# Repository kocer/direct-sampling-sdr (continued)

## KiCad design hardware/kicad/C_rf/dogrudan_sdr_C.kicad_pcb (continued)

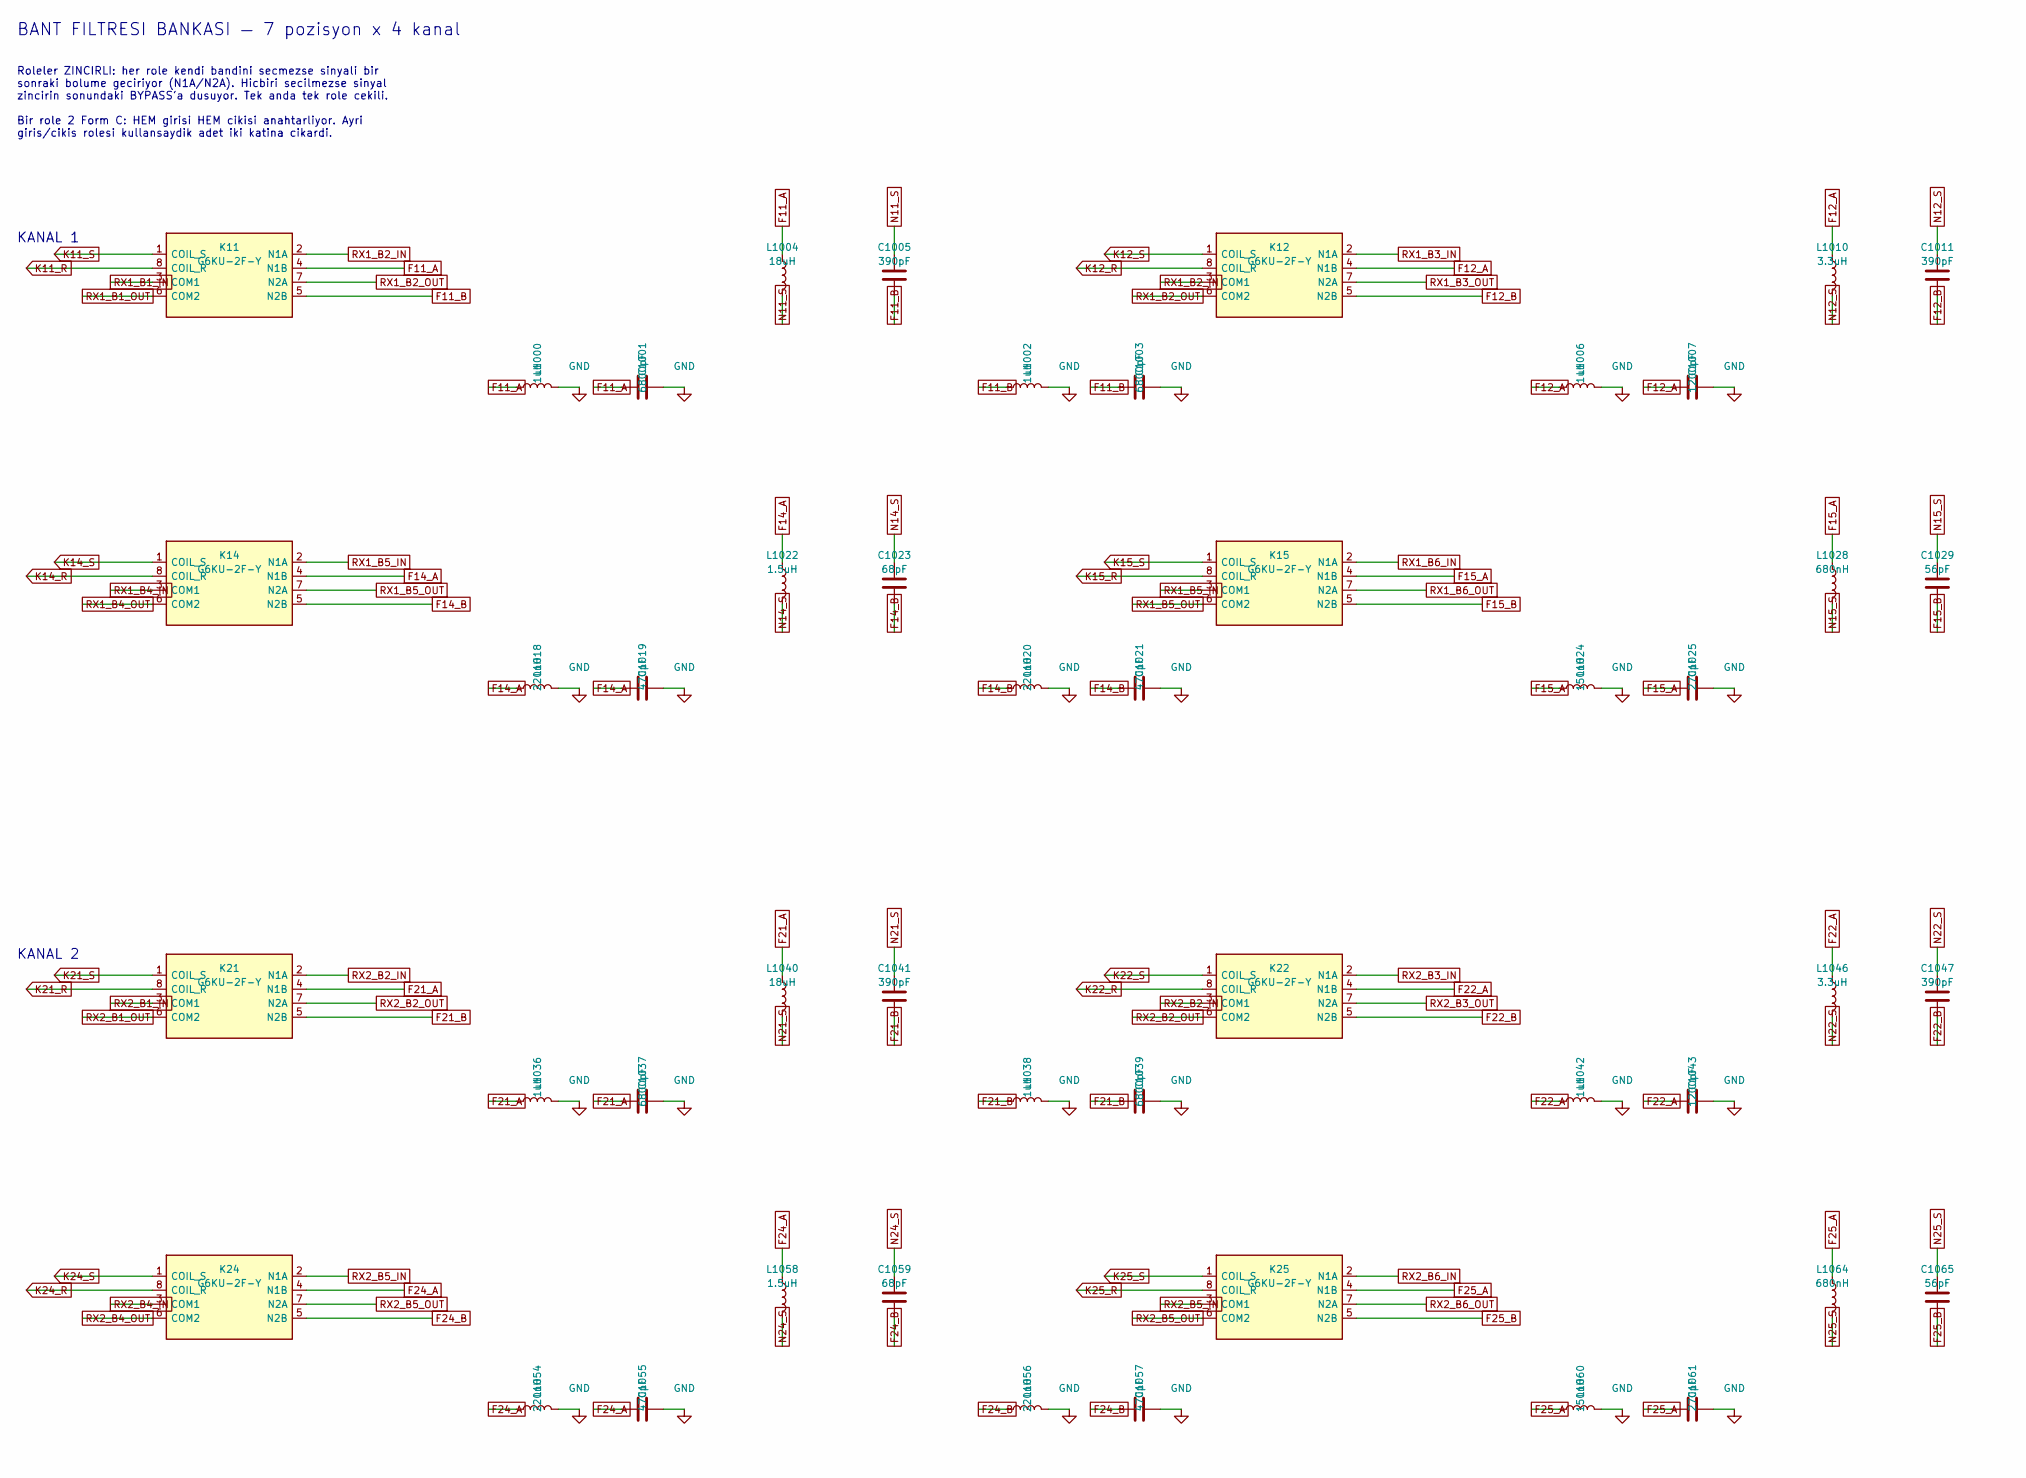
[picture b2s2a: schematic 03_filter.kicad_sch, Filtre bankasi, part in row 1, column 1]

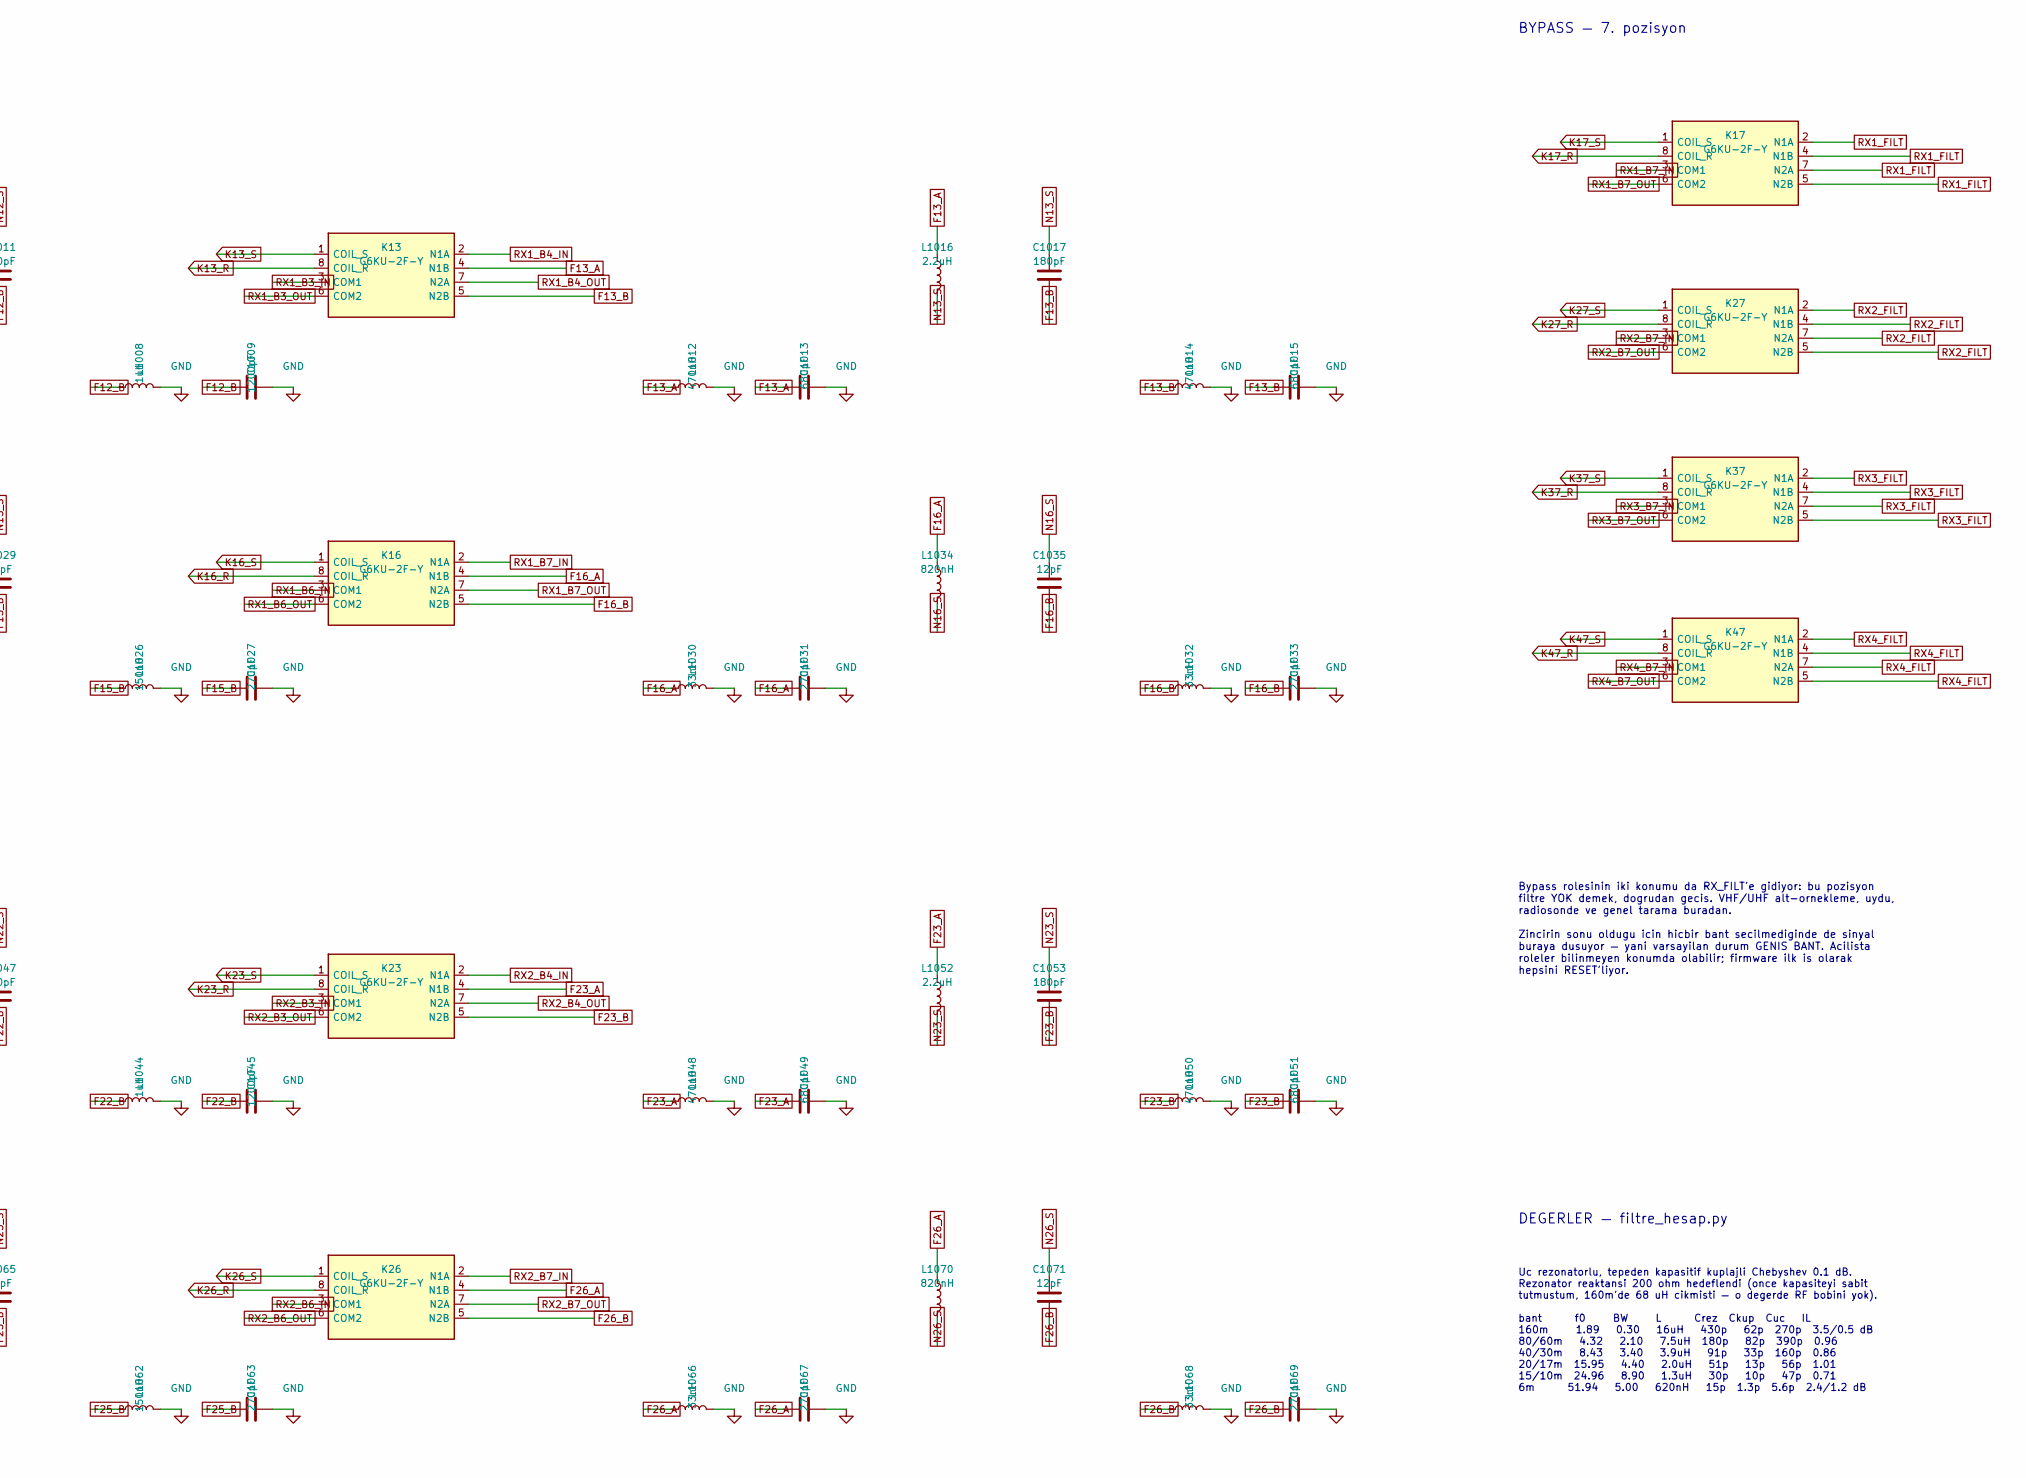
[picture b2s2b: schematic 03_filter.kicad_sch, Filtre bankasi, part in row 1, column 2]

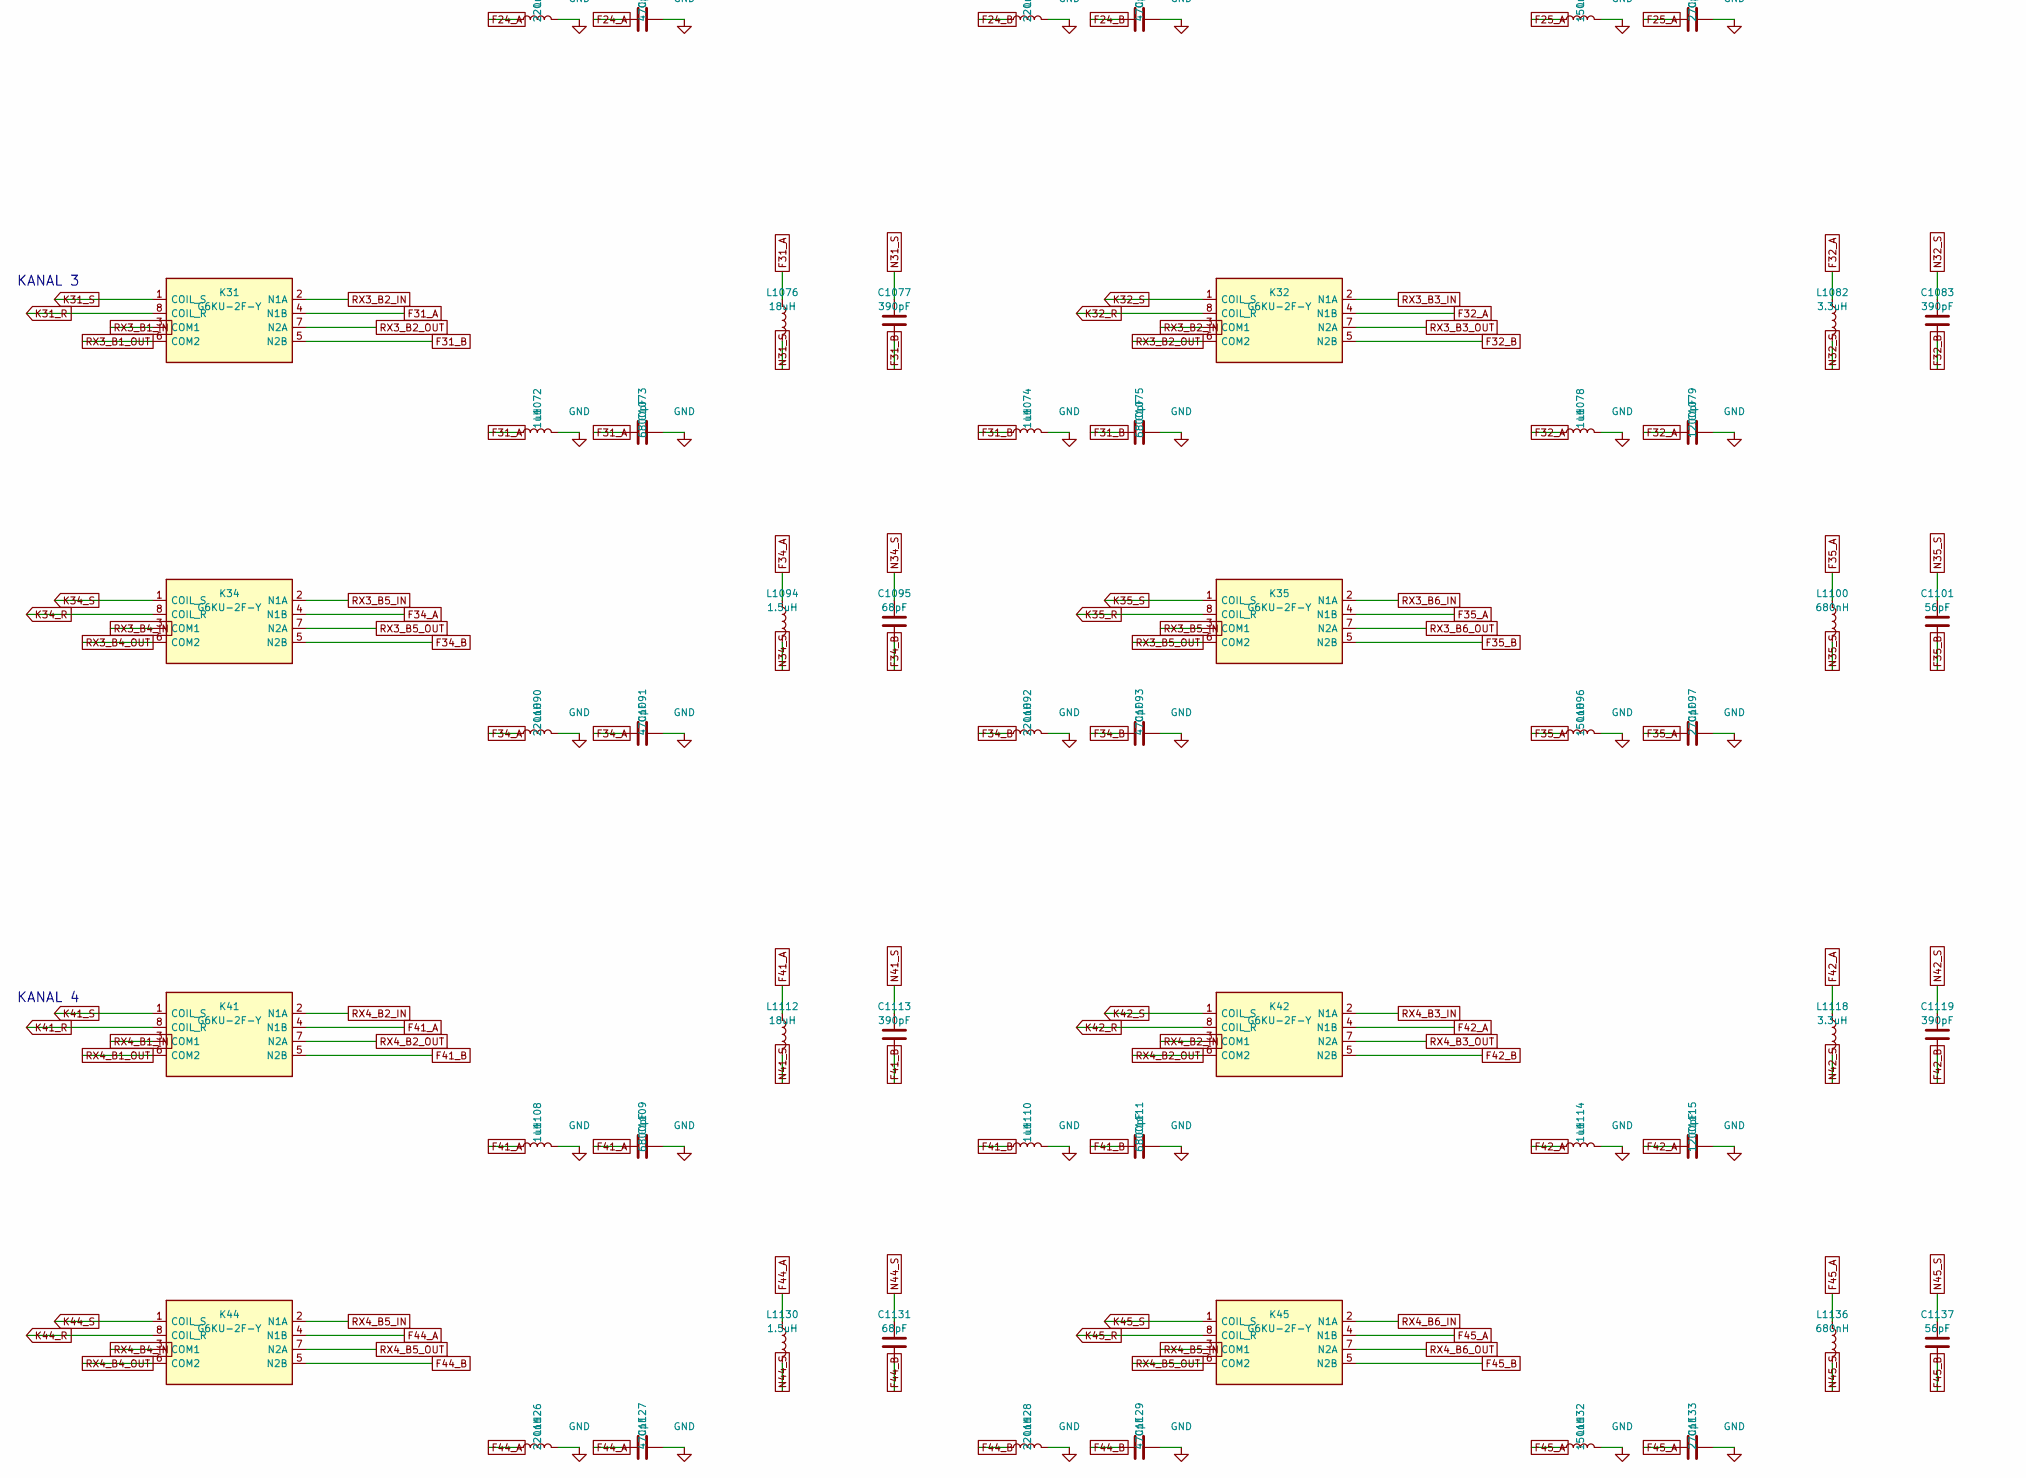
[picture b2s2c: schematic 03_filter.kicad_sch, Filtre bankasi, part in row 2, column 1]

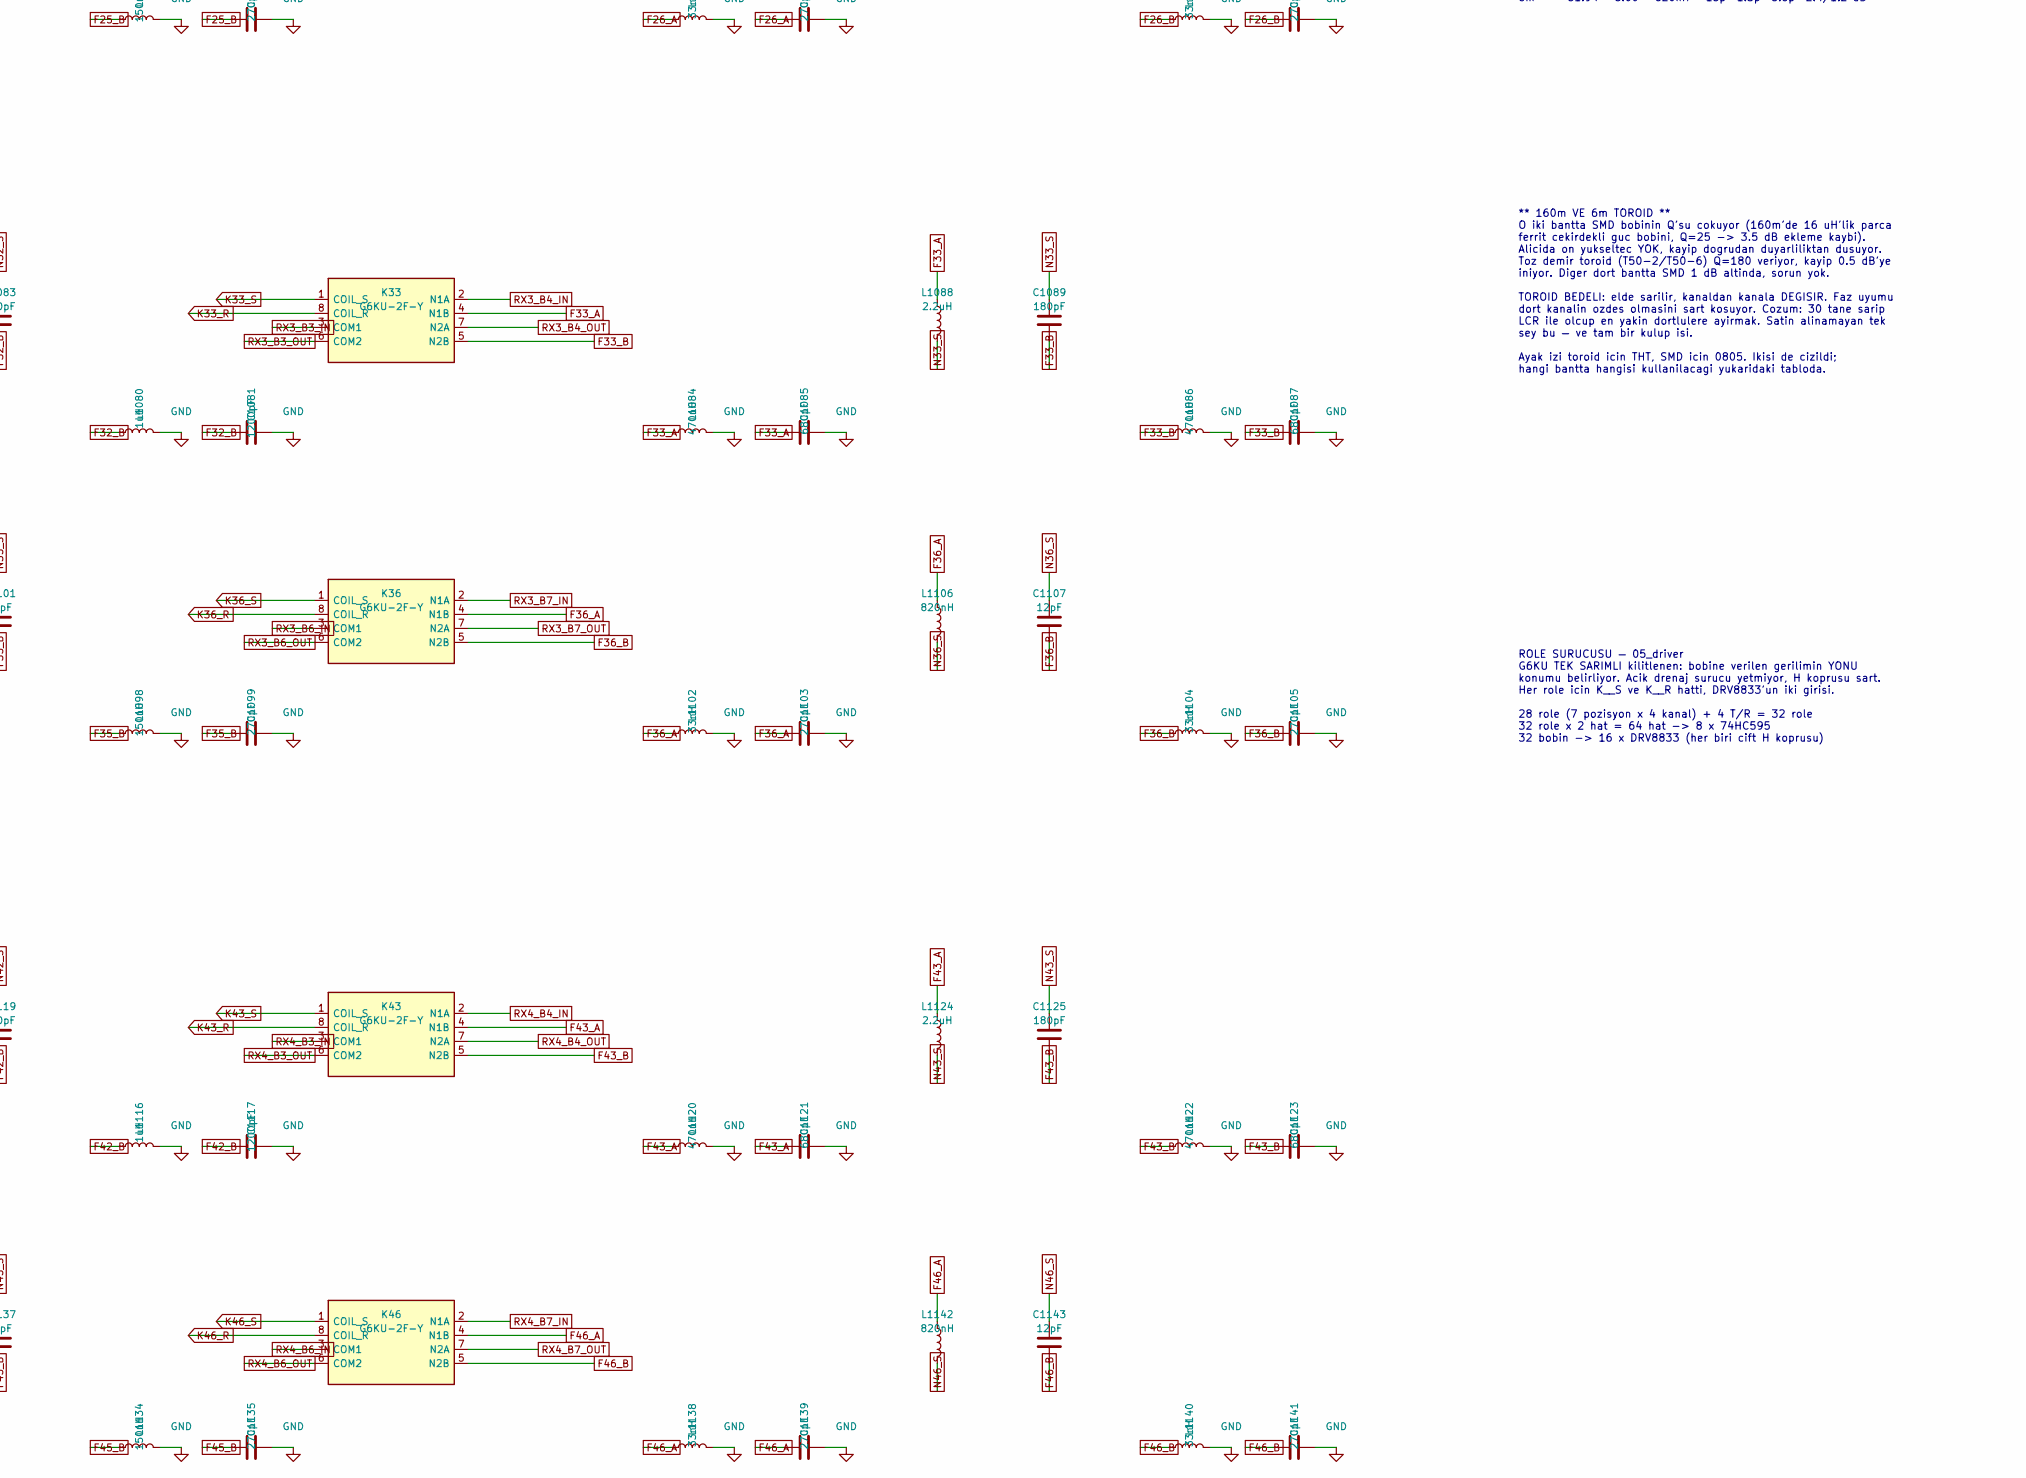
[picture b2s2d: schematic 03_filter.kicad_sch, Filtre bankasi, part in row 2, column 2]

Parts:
C1001, C1003, C1037, C1039, C1073, C1075, C1109, C1111: 6800pF; C_0603_1608Metric
C1005, C1011, C1041, C1047, C1077, C1083, C1113, C1119: 390pF; C_0603_1608Metric
C1007, C1009, C1043, C1045, C1079, C1081, C1115, C1117: 1200pF; C_0603_1608Metric
C1013, C1015, C1049, C1051, C1085, C1087, C1121, C1123: 680pF; C_0603_1608Metric
C1017, C1053, C1089, C1125: 180pF; C_0603_1608Metric
C1019, C1021, C1055, C1057, C1091, C1093, C1127, C1129: 470pF; C_0603_1608Metric
C1023, C1059, C1095, C1131: 68pF; C_0603_1608Metric
C1025, C1027, C1031, C1033, C1061, C1063, C1067, C1069, C1097, C1099, C1103, C1105, C1133, C1135, C1139, C1141: 270pF; C_0603_1608Metric
C1029, C1065, C1101, C1137: 56pF; C_0603_1608Metric
C1035, C1071, C1107, C1143: 12pF; C_0603_1608Metric
K11, K12, K13, K14, K15, K16, K17, K21, K22, K23, K24, K25, K26, K27, K31, K32, K33, K34, K35, K36, K37, K41, K42, K43, K44, K45, K46, K47: G6KU-2F-Y; Relay_DPDT_Omron_G6K-2F-Y
L1000, L1002, L1006, L1008, L1036, L1038, L1042, L1044, L1072, L1074, L1078, L1080, L1108, L1110, L1114, L1116: 1uH; L_1210_3225Metric
L1004, L1040, L1076, L1112: 18uH; L_1210_3225Metric
L1010, L1046, L1082, L1118: 3.3uH; L_1210_3225Metric
L1012, L1014, L1048, L1050, L1084, L1086, L1120, L1122: 470nH; L_0805_2012Metric
L1016, L1052, L1088, L1124: 2.2uH; L_1210_3225Metric
L1018, L1020, L1054, L1056, L1090, L1092, L1126, L1128: 220nH; L_0603_1608Metric
L1022, L1058, L1094, L1130: 1.5uH; L_1210_3225Metric
L1024, L1026, L1060, L1062, L1096, L1098, L1132, L1134: 150nH; L_0603_1608Metric
L1028, L1064, L1100, L1136: 680nH; L_1210_3225Metric
L1030, L1032, L1066, L1068, L1102, L1104, L1138, L1140: 33nH; L_0603_1608Metric
L1034, L1070, L1106, L1142: 820nH; L_1210_3225Metric

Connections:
F11_A: C1001.1, K11.4 (N1B), L1000.1, L1004.1
F11_B: C1003.1, C1005.2, K11.5 (N2B), L1002.1
F12_A: C1007.1, K12.4 (N1B), L1006.1, L1010.1
F12_B: C1009.1, C1011.2, K12.5 (N2B), L1008.1
F13_A: C1013.1, K13.4 (N1B), L1012.1, L1016.1
F13_B: C1015.1, C1017.2, K13.5 (N2B), L1014.1
F14_A: C1019.1, K14.4 (N1B), L1018.1, L1022.1
F14_B: C1021.1, C1023.2, K14.5 (N2B), L1020.1
F15_A: C1025.1, K15.4 (N1B), L1024.1, L1028.1
F15_B: C1027.1, C1029.2, K15.5 (N2B), L1026.1
F16_A: C1031.1, K16.4 (N1B), L1030.1, L1034.1
F16_B: C1033.1, C1035.2, K16.5 (N2B), L1032.1
F21_A: C1037.1, K21.4 (N1B), L1036.1, L1040.1
F21_B: C1039.1, C1041.2, K21.5 (N2B), L1038.1
F22_A: C1043.1, K22.4 (N1B), L1042.1, L1046.1
F22_B: C1045.1, C1047.2, K22.5 (N2B), L1044.1
F23_A: C1049.1, K23.4 (N1B), L1048.1, L1052.1
F23_B: C1051.1, C1053.2, K23.5 (N2B), L1050.1
F24_A: C1055.1, K24.4 (N1B), L1054.1, L1058.1
F24_B: C1057.1, C1059.2, K24.5 (N2B), L1056.1
F25_A: C1061.1, K25.4 (N1B), L1060.1, L1064.1
F25_B: C1063.1, C1065.2, K25.5 (N2B), L1062.1
F26_A: C1067.1, K26.4 (N1B), L1066.1, L1070.1
F26_B: C1069.1, C1071.2, K26.5 (N2B), L1068.1
F31_A: C1073.1, K31.4 (N1B), L1072.1, L1076.1
F31_B: C1075.1, C1077.2, K31.5 (N2B), L1074.1
F32_A: C1079.1, K32.4 (N1B), L1078.1, L1082.1
F32_B: C1081.1, C1083.2, K32.5 (N2B), L1080.1
F33_A: C1085.1, K33.4 (N1B), L1084.1, L1088.1
F33_B: C1087.1, C1089.2, K33.5 (N2B), L1086.1
F34_A: C1091.1, K34.4 (N1B), L1090.1, L1094.1
F34_B: C1093.1, C1095.2, K34.5 (N2B), L1092.1
F35_A: C1097.1, K35.4 (N1B), L1096.1, L1100.1
F35_B: C1099.1, C1101.2, K35.5 (N2B), L1098.1
F36_A: C1103.1, K36.4 (N1B), L1102.1, L1106.1
F36_B: C1105.1, C1107.2, K36.5 (N2B), L1104.1
F41_A: C1109.1, K41.4 (N1B), L1108.1, L1112.1
F41_B: C1111.1, C1113.2, K41.5 (N2B), L1110.1
F42_A: C1115.1, K42.4 (N1B), L1114.1, L1118.1
F42_B: C1117.1, C1119.2, K42.5 (N2B), L1116.1
F43_A: C1121.1, K43.4 (N1B), L1120.1, L1124.1
F43_B: C1123.1, C1125.2, K43.5 (N2B), L1122.1
F44_A: C1127.1, K44.4 (N1B), L1126.1, L1130.1
F44_B: C1129.1, C1131.2, K44.5 (N2B), L1128.1
F45_A: C1133.1, K45.4 (N1B), L1132.1, L1136.1
F45_B: C1135.1, C1137.2, K45.5 (N2B), L1134.1
F46_A: C1139.1, K46.4 (N1B), L1138.1, L1142.1
F46_B: C1141.1, C1143.2, K46.5 (N2B), L1140.1
K11_R: K11.8 (COIL_R); also elsewhere on the board
K11_S: K11.1 (COIL_S); also elsewhere on the board
K12_R: K12.8 (COIL_R); also elsewhere on the board
K12_S: K12.1 (COIL_S); also elsewhere on the board
K13_R: K13.8 (COIL_R); also elsewhere on the board
K13_S: K13.1 (COIL_S); also elsewhere on the board
K14_R: K14.8 (COIL_R); also elsewhere on the board
K14_S: K14.1 (COIL_S); also elsewhere on the board
K15_R: K15.8 (COIL_R); also elsewhere on the board
K15_S: K15.1 (COIL_S); also elsewhere on the board
K16_R: K16.8 (COIL_R); also elsewhere on the board
K16_S: K16.1 (COIL_S); also elsewhere on the board
K17_R: K17.8 (COIL_R); also elsewhere on the board
K17_S: K17.1 (COIL_S); also elsewhere on the board
K21_R: K21.8 (COIL_R); also elsewhere on the board
K21_S: K21.1 (COIL_S); also elsewhere on the board
K22_R: K22.8 (COIL_R); also elsewhere on the board
K22_S: K22.1 (COIL_S); also elsewhere on the board
K23_R: K23.8 (COIL_R); also elsewhere on the board
K23_S: K23.1 (COIL_S); also elsewhere on the board
K24_R: K24.8 (COIL_R); also elsewhere on the board
K24_S: K24.1 (COIL_S); also elsewhere on the board
K25_R: K25.8 (COIL_R); also elsewhere on the board
K25_S: K25.1 (COIL_S); also elsewhere on the board
K26_R: K26.8 (COIL_R); also elsewhere on the board
K26_S: K26.1 (COIL_S); also elsewhere on the board
K27_R: K27.8 (COIL_R); also elsewhere on the board
K27_S: K27.1 (COIL_S); also elsewhere on the board
K31_R: K31.8 (COIL_R); also elsewhere on the board
K31_S: K31.1 (COIL_S); also elsewhere on the board
K32_R: K32.8 (COIL_R); also elsewhere on the board
K32_S: K32.1 (COIL_S); also elsewhere on the board
K33_R: K33.8 (COIL_R); also elsewhere on the board
K33_S: K33.1 (COIL_S); also elsewhere on the board
K34_R: K34.8 (COIL_R); also elsewhere on the board
K34_S: K34.1 (COIL_S); also elsewhere on the board
K35_R: K35.8 (COIL_R); also elsewhere on the board
K35_S: K35.1 (COIL_S); also elsewhere on the board
K36_R: K36.8 (COIL_R); also elsewhere on the board
K36_S: K36.1 (COIL_S); also elsewhere on the board
K37_R: K37.8 (COIL_R); also elsewhere on the board
K37_S: K37.1 (COIL_S); also elsewhere on the board
K41_R: K41.8 (COIL_R); also elsewhere on the board
K41_S: K41.1 (COIL_S); also elsewhere on the board
K42_R: K42.8 (COIL_R); also elsewhere on the board
K42_S: K42.1 (COIL_S); also elsewhere on the board
K43_R: K43.8 (COIL_R); also elsewhere on the board
K43_S: K43.1 (COIL_S); also elsewhere on the board
K44_R: K44.8 (COIL_R); also elsewhere on the board
K44_S: K44.1 (COIL_S); also elsewhere on the board
K45_R: K45.8 (COIL_R); also elsewhere on the board
K45_S: K45.1 (COIL_S); also elsewhere on the board
K46_R: K46.8 (COIL_R); also elsewhere on the board
K46_S: K46.1 (COIL_S); also elsewhere on the board
K47_R: K47.8 (COIL_R); also elsewhere on the board
K47_S: K47.1 (COIL_S); also elsewhere on the board
N11_S: C1005.1, L1004.2
N12_S: C1011.1, L1010.2
N13_S: C1017.1, L1016.2
N14_S: C1023.1, L1022.2
N15_S: C1029.1, L1028.2
N16_S: C1035.1, L1034.2
N21_S: C1041.1, L1040.2
N22_S: C1047.1, L1046.2
N23_S: C1053.1, L1052.2
N24_S: C1059.1, L1058.2
N25_S: C1065.1, L1064.2
N26_S: C1071.1, L1070.2
N31_S: C1077.1, L1076.2
N32_S: C1083.1, L1082.2
N33_S: C1089.1, L1088.2
N34_S: C1095.1, L1094.2
N35_S: C1101.1, L1100.2
N36_S: C1107.1, L1106.2
N41_S: C1113.1, L1112.2
N42_S: C1119.1, L1118.2
N43_S: C1125.1, L1124.2
N44_S: C1131.1, L1130.2
N45_S: C1137.1, L1136.2
N46_S: C1143.1, L1142.2
RX1_B1_IN: K11.3 (COM1); also elsewhere on the board
RX1_B1_OUT: K11.6 (COM2); also elsewhere on the board
RX1_B2_IN: K11.2 (N1A), K12.3 (COM1)
RX1_B2_OUT: K11.7 (N2A), K12.6 (COM2)
RX1_B3_IN: K12.2 (N1A), K13.3 (COM1)
RX1_B3_OUT: K12.7 (N2A), K13.6 (COM2)
RX1_B4_IN: K13.2 (N1A), K14.3 (COM1)
RX1_B4_OUT: K13.7 (N2A), K14.6 (COM2)
RX1_B5_IN: K14.2 (N1A), K15.3 (COM1)
RX1_B5_OUT: K14.7 (N2A), K15.6 (COM2)
RX1_B6_IN: K15.2 (N1A), K16.3 (COM1)
RX1_B6_OUT: K15.7 (N2A), K16.6 (COM2)
RX1_B7_IN: K16.2 (N1A), K17.3 (COM1)
RX1_B7_OUT: K16.7 (N2A), K17.6 (COM2)
RX1_FILT: K17.2 (N1A), K17.4 (N1B), K17.5 (N2B), K17.7 (N2A); also elsewhere on the board
RX2_B1_IN: K21.3 (COM1); also elsewhere on the board
RX2_B1_OUT: K21.6 (COM2); also elsewhere on the board
RX2_B2_IN: K21.2 (N1A), K22.3 (COM1)
RX2_B2_OUT: K21.7 (N2A), K22.6 (COM2)
RX2_B3_IN: K22.2 (N1A), K23.3 (COM1)
RX2_B3_OUT: K22.7 (N2A), K23.6 (COM2)
RX2_B4_IN: K23.2 (N1A), K24.3 (COM1)
RX2_B4_OUT: K23.7 (N2A), K24.6 (COM2)
RX2_B5_IN: K24.2 (N1A), K25.3 (COM1)
RX2_B5_OUT: K24.7 (N2A), K25.6 (COM2)
RX2_B6_IN: K25.2 (N1A), K26.3 (COM1)
RX2_B6_OUT: K25.7 (N2A), K26.6 (COM2)
RX2_B7_IN: K26.2 (N1A), K27.3 (COM1)
RX2_B7_OUT: K26.7 (N2A), K27.6 (COM2)
RX2_FILT: K27.2 (N1A), K27.4 (N1B), K27.5 (N2B), K27.7 (N2A); also elsewhere on the board
RX3_B1_IN: K31.3 (COM1); also elsewhere on the board
RX3_B1_OUT: K31.6 (COM2); also elsewhere on the board
RX3_B2_IN: K31.2 (N1A), K32.3 (COM1)
RX3_B2_OUT: K31.7 (N2A), K32.6 (COM2)
RX3_B3_IN: K32.2 (N1A), K33.3 (COM1)
RX3_B3_OUT: K32.7 (N2A), K33.6 (COM2)
RX3_B4_IN: K33.2 (N1A), K34.3 (COM1)
RX3_B4_OUT: K33.7 (N2A), K34.6 (COM2)
RX3_B5_IN: K34.2 (N1A), K35.3 (COM1)
RX3_B5_OUT: K34.7 (N2A), K35.6 (COM2)
RX3_B6_IN: K35.2 (N1A), K36.3 (COM1)
RX3_B6_OUT: K35.7 (N2A), K36.6 (COM2)
RX3_B7_IN: K36.2 (N1A), K37.3 (COM1)
RX3_B7_OUT: K36.7 (N2A), K37.6 (COM2)
RX3_FILT: K37.2 (N1A), K37.4 (N1B), K37.5 (N2B), K37.7 (N2A); also elsewhere on the board
RX4_B1_IN: K41.3 (COM1); also elsewhere on the board
RX4_B1_OUT: K41.6 (COM2); also elsewhere on the board
RX4_B2_IN: K41.2 (N1A), K42.3 (COM1)
RX4_B2_OUT: K41.7 (N2A), K42.6 (COM2)
RX4_B3_IN: K42.2 (N1A), K43.3 (COM1)
RX4_B3_OUT: K42.7 (N2A), K43.6 (COM2)
RX4_B4_IN: K43.2 (N1A), K44.3 (COM1)
RX4_B4_OUT: K43.7 (N2A), K44.6 (COM2)
RX4_B5_IN: K44.2 (N1A), K45.3 (COM1)
RX4_B5_OUT: K44.7 (N2A), K45.6 (COM2)
RX4_B6_IN: K45.2 (N1A), K46.3 (COM1)
RX4_B6_OUT: K45.7 (N2A), K46.6 (COM2)
RX4_B7_IN: K46.2 (N1A), K47.3 (COM1)
RX4_B7_OUT: K46.7 (N2A), K47.6 (COM2)
RX4_FILT: K47.2 (N1A), K47.4 (N1B), K47.5 (N2B), K47.7 (N2A); also elsewhere on the board

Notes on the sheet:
KANAL 4
Uc rezonatorlu, tepeden kapasitif kuplajli Chebyshev 0.1 dB. Rezonator reaktansi 200 ohm hedeflendi (once kapasiteyi sabit tutmustum, 160m'de 68 uH cikmisti — o degerde RF bobini yok). bant f0 BW L Crez Ckup Cuc IL 160m 1.89 0.30 16uH 430p 62p 270p 3.5/0.5 dB 80/60m 4.32 2.10 7.5uH 180p 82p 390p 0.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
KANAL 2
BANT FILTRESI BANKASI — 7 pozisyon x 4 kanal
** 160m VE 6m TOROID ** O iki bantta SMD bobinin Q'su cokuyor (160m'de 16 uH'lik parca ferrit cekirdekli guc bobini, Q=25 -> 3.5 dB ekleme kaybi). Alicida on yukseltec YOK, kayip dogrudan duyarliliktan dusuyor. Toz demir toroid (T50-2/T50-6) Q=180 veriyor, kayip 0.5 dB'ye iniyor. Diger dort bantta 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
DEGERLER — filtre_hesap.py
KANAL 3
ROLE SURUCUSU — 05_driver G6KU TEK SARIMLI kilitlenen: bobine verilen gerilimin YONU konumu belirliyor. Acik drenaj surucu yetmiyor, H koprusu sart. Her role icin K__S ve K__R hatti, DRV8833'un iki girisi. 28 role (7 pozisyon x 4 kanal) + 4 T/R = 32 role 32 role x 2 hat = 64 hat -> 8 x 74HC595 32 b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
Roleler ZINCIRLI: her role kendi bandini secmezse sinyali bir sonraki bolume geciriyor (N1A/N2A). Hicbiri secilmezse sinyal zincirin sonundaki BYPASS'a dusuyor. Tek anda tek role cekili. Bir role 2 Form C: HEM girisi HEM cikisi anahtarliyor. Ayri giris/cikis rolesi kullansaydik adet iki katina cika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
Bypass rolesinin iki konumu da RX_FILT'e gidiyor: bu pozisyon filtre YOK demek, dogrudan gecis. VHF/UHF alt-ornekleme, uydu, radiosonde ve genel tarama buradan. Zincirin sonu oldugu icin hicbir bant secilmediginde de sinyal buraya dusuyor — yani varsayilan durum GENIS BANT. Acilista roleler bilinme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
KANAL 1
BYPASS — 7. pozisyon
